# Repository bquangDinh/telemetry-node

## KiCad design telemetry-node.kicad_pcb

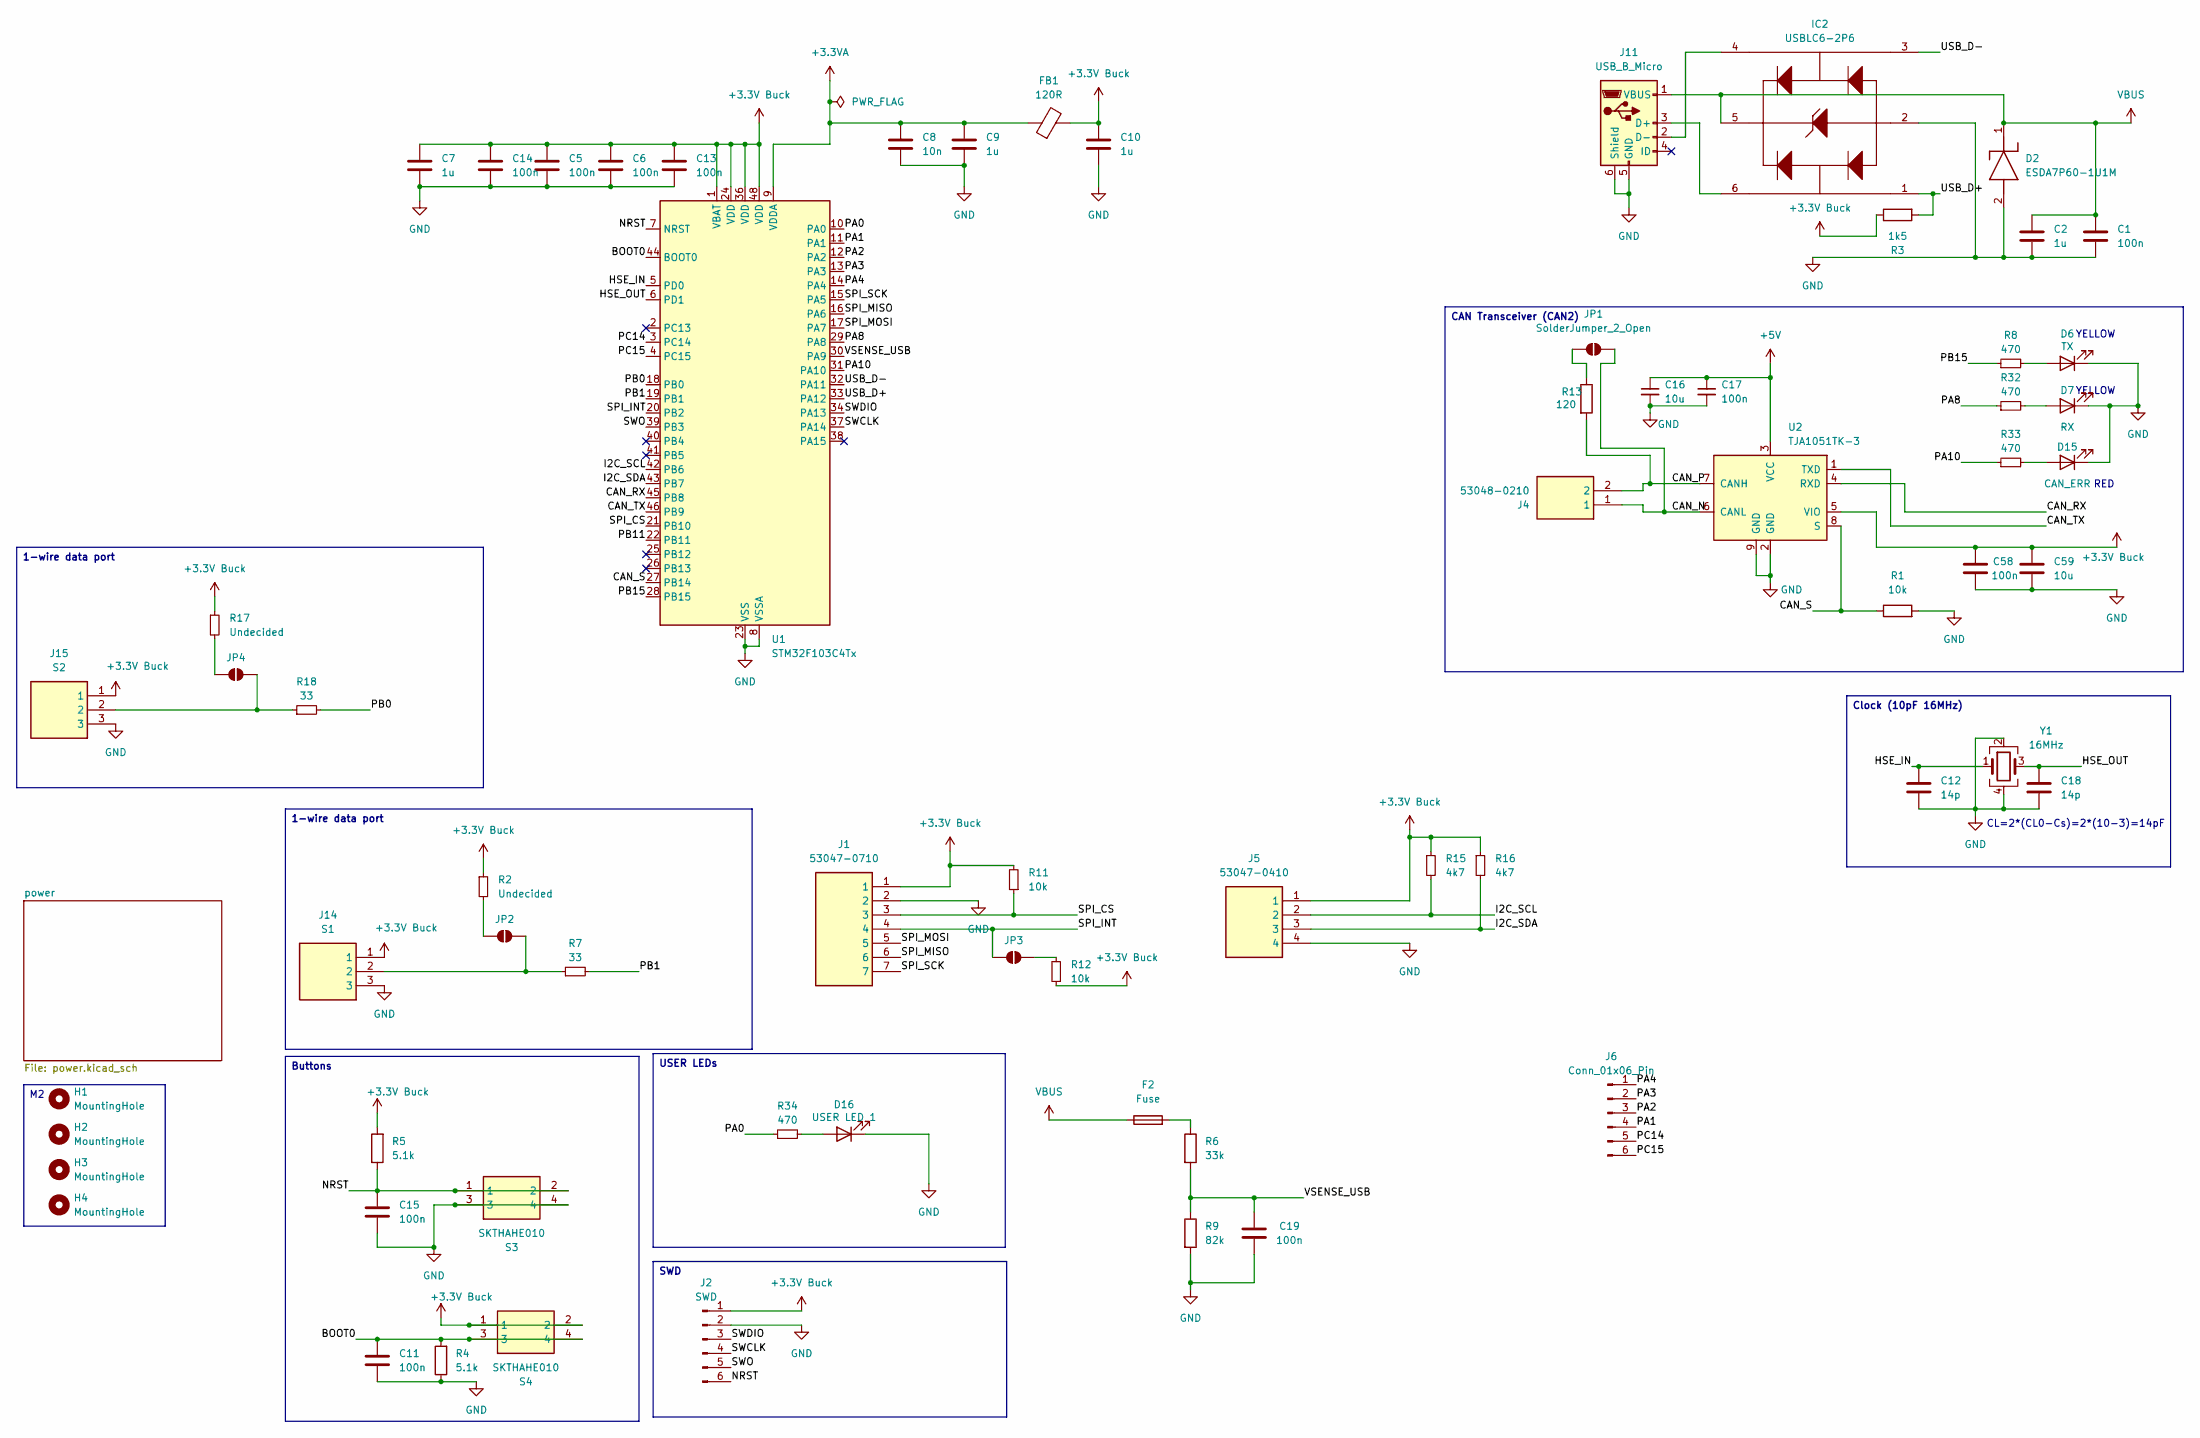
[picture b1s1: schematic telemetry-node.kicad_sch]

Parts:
C1, C5, C6, C11, C13, C14, C15, C17, C19, C58: 100n; C_0603_1608Metric_Pad1.08x0.95mm_HandSolder
C2, C7, C9, C10: 1u; C_0805_2012Metric_Pad1.18x1.45mm_HandSolder
C8: 10n; C_0603_1608Metric_Pad1.08x0.95mm_HandSolder
C12, C18: 14p; C_0603_1608Metric_Pad1.08x0.95mm_HandSolder
C16, C59: 10u; C_0805_2012Metric_Pad1.18x1.45mm_HandSolder
D2: ESDA7P60-1U1M; ESDA7P601U1M; Mouser Part Number 511-ESDA7P60-1U1M
D6: TX; LED_0805_2012Metric_Pad1.15x1.40mm_HandSolder
D7: RX; LED_0805_2012Metric_Pad1.15x1.40mm_HandSolder
D15: CAN_ERR; LED_0805_2012Metric_Pad1.15x1.40mm_HandSolder
D16: USER LED 1; LED_0805_2012Metric_Pad1.15x1.40mm_HandSolder
F2: Fuse; Fuse_0603_1608Metric_Pad1.05x0.95mm_HandSolder
FB1: 120R; L_0805_2012Metric_Pad1.05x1.20mm_HandSolder
H1, H2, H3, H4: MountingHole; MountingHole_2.2mm_M2
IC2: USBLC6-2P6; USBLC62P6; Mouser Part Number 511-USBLC6-2P6
J1: 53047-0710; 530470710; Mouser Part Number 538-53047-0710
J2: SWD; PinHeader_1x06_P2.00mm_Vertical
J4: 53048-0210; SHDRRA2W35P0X125_1X2_425X550X350P; Mouser Part Number 538-53048-0210
J5: 53047-0410; 530470410; Mouser Part Number 538-53047-0410
J6: Conn_01x06_Pin; PinHeader_1x06_P2.00mm_Vertical
J11: USB_B_Micro; USB_Micro-B_Wuerth_629105150521
J14: S1; 530470310; Mouser Part Number 538-53047-0310
J15: S2; 530470310; Mouser Part Number 538-53047-0310
JP1, JP2, JP3, JP4: SolderJumper_2_Open; SolderJumper-2_P1.3mm_Open_RoundedPad1.0x1.5mm
R1, R11, R12: 10k; R_0603_1608Metric_Pad0.98x0.95mm_HandSolder
R2, R17: Undecided; R_0603_1608Metric_Pad0.98x0.95mm_HandSolder
R3: 1k5; R_0603_1608Metric_Pad0.98x0.95mm_HandSolder
R4, R5: 5.1k; R_0603_1608Metric_Pad0.98x0.95mm_HandSolder
R6: 33k; R_0603_1608Metric_Pad0.98x0.95mm_HandSolder
R7, R18: 33; R_0603_1608Metric_Pad0.98x0.95mm_HandSolder
R8, R32, R33, R34: 470; R_0603_1608Metric_Pad0.98x0.95mm_HandSolder
R9: 82k; R_0603_1608Metric_Pad0.98x0.95mm_HandSolder
R13: 120; R_0603_1608Metric_Pad0.98x0.95mm_HandSolder
R15, R16: 4k7; R_0603_1608Metric_Pad0.98x0.95mm_HandSolder
S3, S4: SKTHAHE010; Mouser Part Number 688-SKTHAHE010
U1: STM32F103C4Tx; LQFP-48_7x7mm_P0.5mm
U2: TJA1051TK-3; DFN-8-1EP_3x3mm_P0.65mm_EP1.55x2.4mm
Y1: 16MHz; Crystal_SMD_3225-4Pin_3.2x2.5mm

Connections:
+3.3V Buck: C5.1, C6.1, C7.1, C10.1, C13.1, C14.1, C58.2, C59.2, FB1.2, J1.1, J2.1, J5.1, J14.1, J15.1, R2.1, R3.1, R5.2, R11.2, R12.1, R15.1, R16.1, R17.1, S4.1, S4.2, U1.1 (VBAT), U1.24 (VDD), U1.36 (VDD), U1.48 (VDD), U2.5 (VIO); also elsewhere on the board
+3.3VA: C8.1, C9.1, FB1.1, U1.9 (VDDA)
+5V: C16.1, C17.1, U2.3 (VCC); also elsewhere on the board
/BOOT0: C11.1, R4.2, S4.3, S4.4, U1.44 (BOOT0)
/CAN_N: J4.1, JP1.2 (B), U2.6 (CANL)
/CAN_P: J4.2, R13.2, U2.7 (CANH)
/CAN_RX: U1.45 (PB8), U2.4 (RXD)
/CAN_S: R1.1, U1.27 (PB14), U2.8 (S)
/CAN_TX: U1.46 (PB9), U2.1 (TXD)
/HSE_IN: C12.1, U1.5 (PD0), Y1.1
/HSE_OUT: C18.1, U1.6 (PD1), Y1.3
/I2C_SCL: J5.2, R15.2, U1.42 (PB6)
/I2C_SDA: J5.3, R16.2, U1.43 (PB7)
/NRST: C15.1, J2.6, R5.1, S3.1, S3.2, U1.7 (NRST)
/PA0: R34.1, U1.10 (PA0)
/PA1: J6.4, U1.11 (PA1)
/PA2: J6.3, U1.12 (PA2)
/PA3: J6.2, U1.13 (PA3)
/PA4: J6.1, U1.14 (PA4)
/PA8: R32.1, U1.29 (PA8)
/PA10: R33.1, U1.31 (PA10)
/PB0: R18.2, U1.18 (PB0)
/PB1: R7.2, U1.19 (PB1)
/PB11: U1.22 (PB11)
/PB15: R8.1, U1.28 (PB15)
/PC14: J6.5, U1.3 (PC14)
/PC15: J6.6, U1.4 (PC15)
/SPI_CS: J1.3, R11.1, U1.21 (PB10)
/SPI_INT: J1.4, JP3.1 (A), U1.20 (PB2)
/SPI_MISO: J1.6, U1.16 (PA6)
/SPI_MOSI: J1.5, U1.17 (PA7)
/SPI_SCK: J1.7, U1.15 (PA5)
/SWCLK: J2.4, U1.37 (PA14)
/SWDIO: J2.3, U1.34 (PA13)
/SWO: J2.5, U1.39 (PB3)
/USB_D+: IC2.1 (I/O1_1), R3.2, U1.33 (PA12)
/USB_D-: IC2.3 (I/O2_1), U1.32 (PA11)
/VSENSE_USB: C19.1, R6.2, R9.1, U1.30 (PA9)
GND: C1.2, C2.2, C5.2, C6.2, C7.2, C8.2, C9.2, C10.2, C11.2, C12.2, C13.2, C14.2, C15.2, C16.2, C17.2, C18.2, C19.2, C58.1, C59.1, D2.2 (A), D6.1 (K), D7.1 (K), D15.1 (K), D16.1 (K), IC2.2 (GND), J1.2, J2.2, J5.4, J11.5 (GND), J11.6 (Shield), J14.3, J15.3, R1.2, R4.1, R9.2, S3.3, S3.4, U1.8 (VSSA), U1.23 (VSS), U1.35 (VSS), U1.47 (VSS), U2.2 (GND), U2.9 (GND), Y1.2, Y1.4; also elsewhere on the board
unnamed: D6.2 (A), R8.2
unnamed: D7.2 (A), R32.2
unnamed: D15.2 (A), R33.2
unnamed: D16.2 (A), R34.2
unnamed: F2.2, R6.1
unnamed: IC2.6 (I/O1_2), J11.3 (D+)
unnamed: IC2.4 (I/O2_2), J11.2 (D-)
unnamed: JP1.1 (A), R13.1
unnamed: JP2.1 (A), R2.2
unnamed: J14.2, JP2.2 (B), R7.1
unnamed: JP3.2 (B), R12.2
unnamed: JP4.1 (A), R17.2
unnamed: J15.2, JP4.2 (B), R18.1
VBUS: C1.1, C2.1, D2.1 (K), F2.1, IC2.5 (VBUS), J11.1 (VBUS)

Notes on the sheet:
RED
YELLOW
CL=2*(CL0-Cs)=2*(10-3)=14pF
CAN Transceiver (CAN2)
Buttons
USER LEDs
1-wire data port
Clock (10pF 16MHz)
SWD

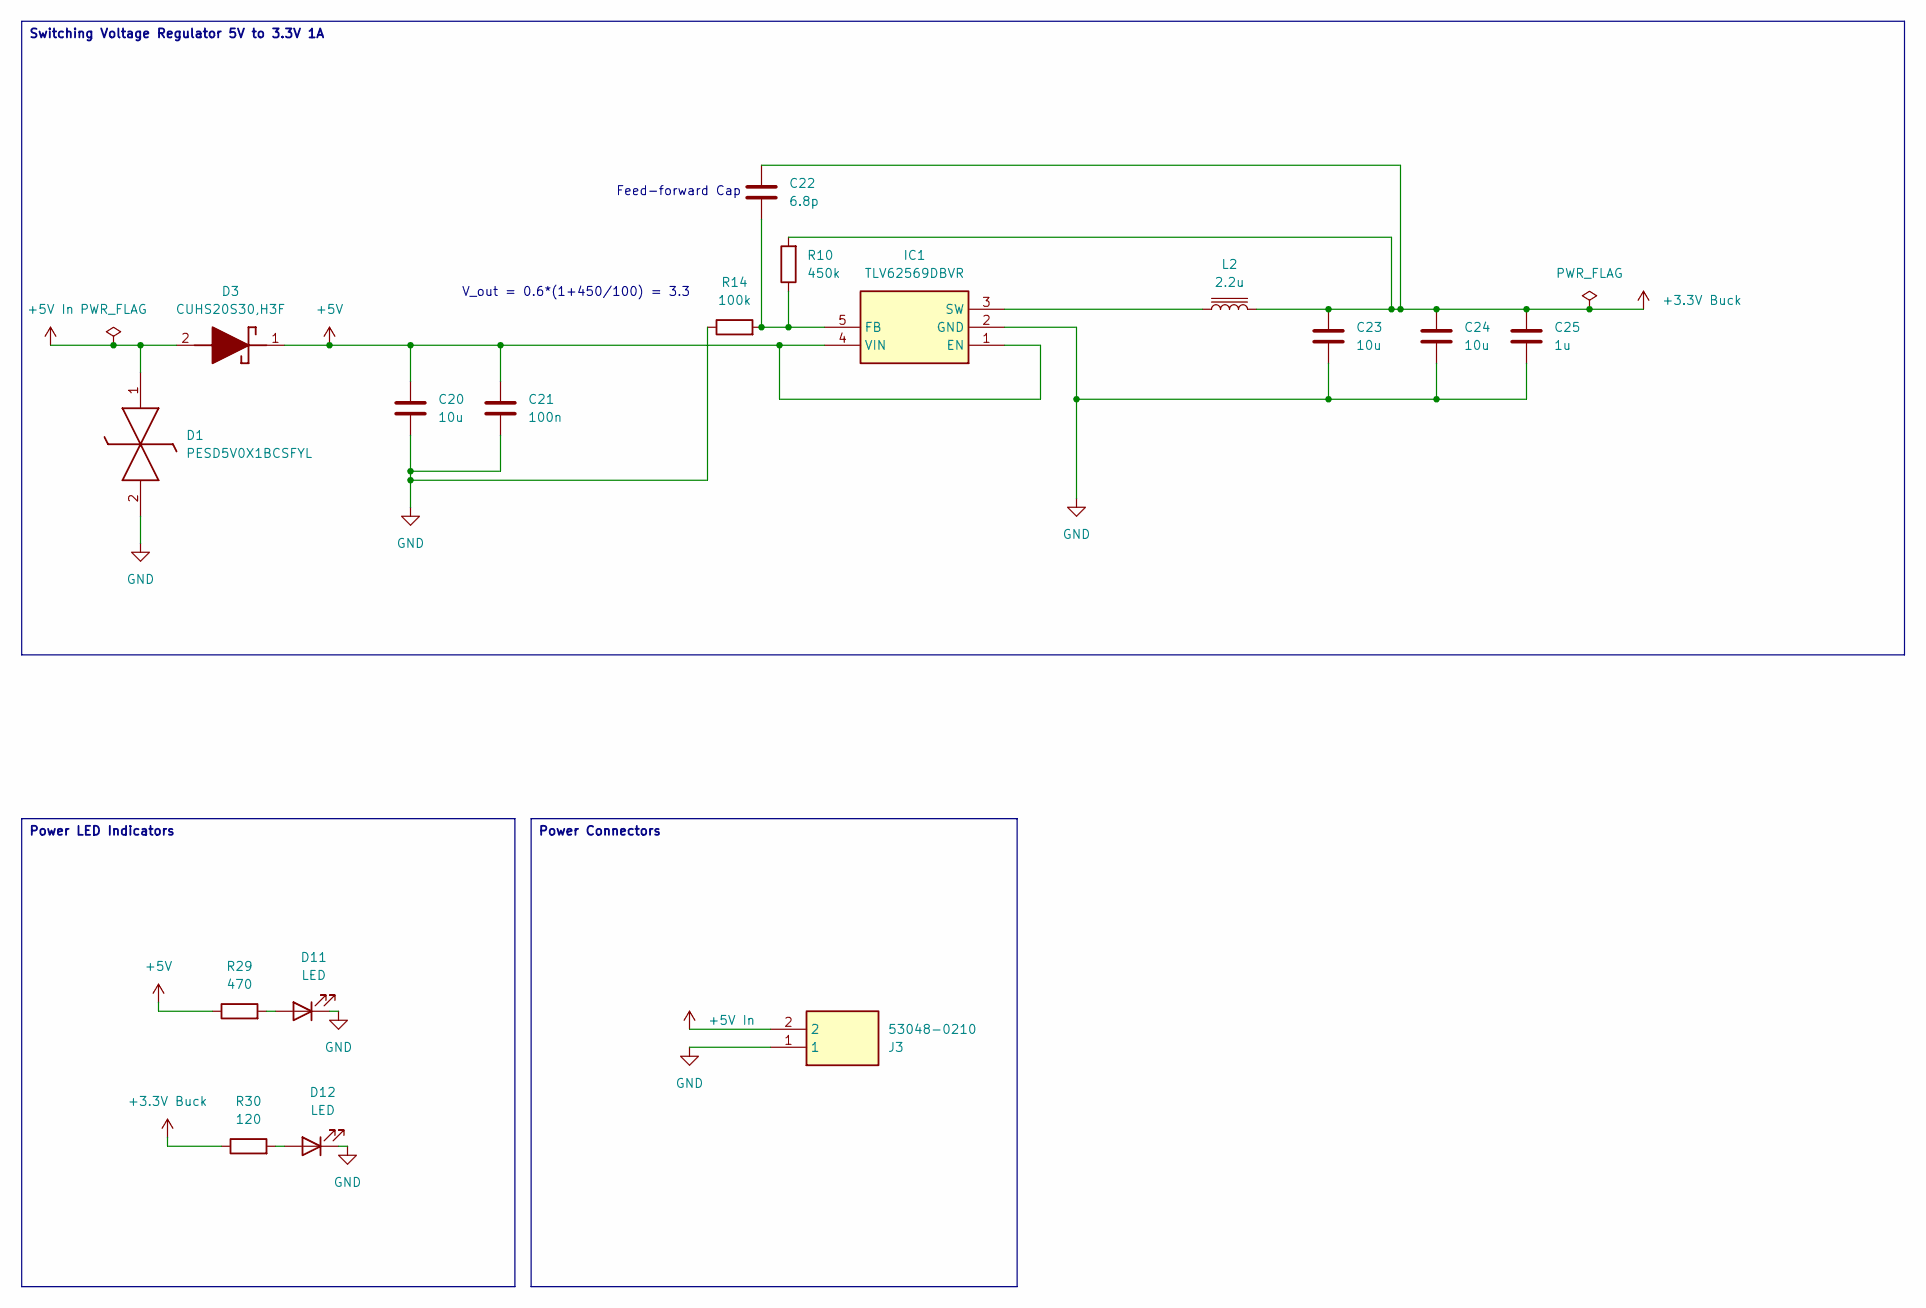
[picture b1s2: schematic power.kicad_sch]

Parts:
C20, C23, C24: 10u; C_0805_2012Metric_Pad1.18x1.45mm_HandSolder
C21: 100n; C_0603_1608Metric_Pad1.08x0.95mm_HandSolder
C22: 6.8p; C_0805_2012Metric_Pad1.18x1.45mm_HandSolder
C25: 1u; C_0805_2012Metric_Pad1.18x1.45mm_HandSolder
D1: PESD5V0X1BCSFYL; PMEG3005AESFYL; Mouser Part Number 771-PESD5V0X1BCSFYL
D3: CUHS20S30,H3F; CUHS20S40H3F; Mouser Part Number 757-CUHS20S30H3F
D11, D12: LED; LED_0805_2012Metric_Pad1.15x1.40mm_HandSolder
IC1: TLV62569DBVR; SOT95P280X145-5N; Mouser Part Number 595-TLV62569DBVR
J3: 53048-0210; SHDRRA2W35P0X125_1X2_425X550X350P; Mouser Part Number 538-53048-0210
L2: 2.2u; LQM2HPZ3R3MJ0B
R10: 450k; R_0805_2012Metric_Pad1.20x1.40mm_HandSolder
R14: 100k; R_0805_2012Metric_Pad1.20x1.40mm_HandSolder
R29: 470; R_0603_1608Metric_Pad0.98x0.95mm_HandSolder
R30: 120; R_0603_1608Metric_Pad0.98x0.95mm_HandSolder

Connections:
+3.3V Buck: C22.2, C23.1, C24.1, C25.1, L2.2, R10.2, R30.1; also elsewhere on the board
+5V: C20.2, C21.1, D3.1 (K), IC1.1 (EN), IC1.4 (VIN), R29.1; also elsewhere on the board
+5V In: D1.1 (K1), D3.2 (A), J3.2
GND: C20.1, C21.2, C23.2, C24.2, C25.2, D1.2 (K2), D11.1 (K), D12.1 (K), IC1.2 (GND), J3.1, R14.1; also elsewhere on the board
unnamed: D11.2 (A), R29.2
unnamed: D12.2 (A), R30.2
unnamed: C22.1, IC1.5 (FB), R10.1, R14.2
unnamed: IC1.3 (SW), L2.1

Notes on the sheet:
Feed-forward Cap
V_out = 0.6*(1+450/100) = 3.3
Power LED Indicators
Power Connectors
Switching Voltage Regulator 5V to 3.3V 1A

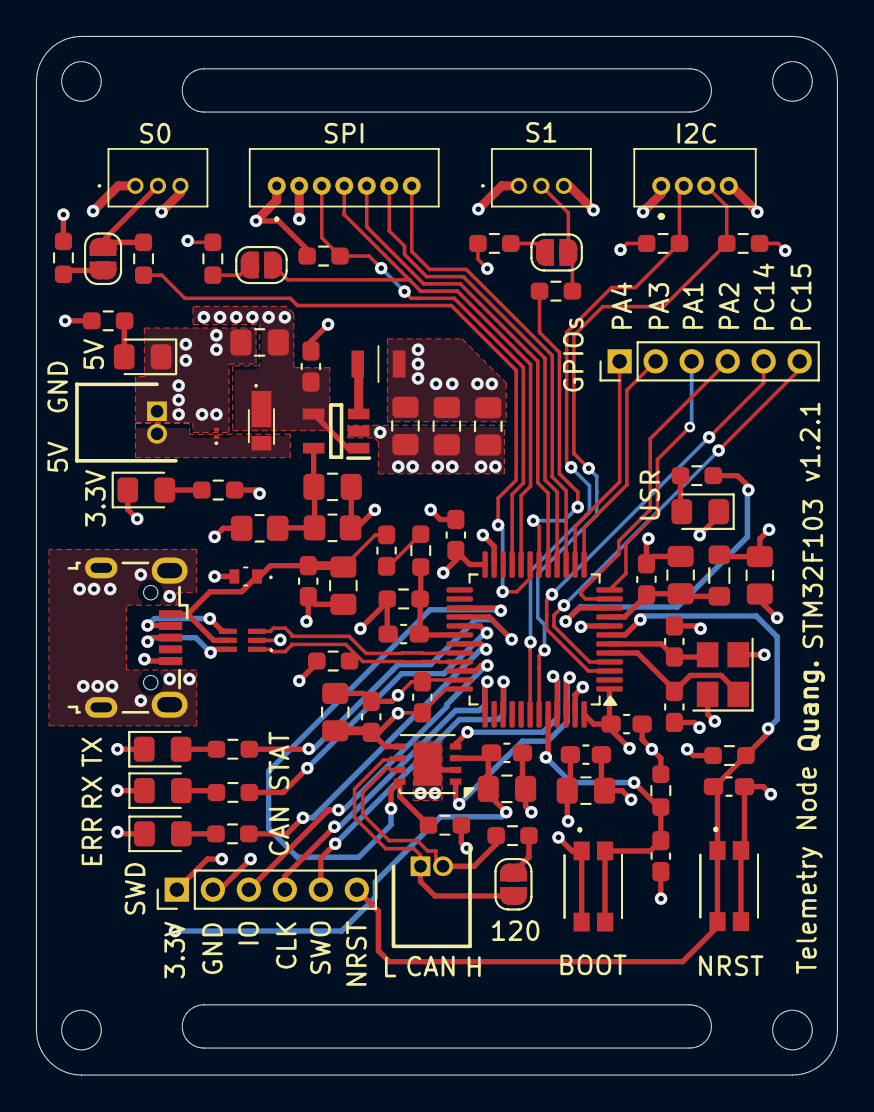
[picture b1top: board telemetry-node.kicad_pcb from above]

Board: 4 copper layers, 44.5 x 57.7 mm, 84 parts (0 on the bottom side), 57 nets.

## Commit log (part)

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2026-02-15 Changed things
2026-02-17 Fixed things
2026-03-14 Added temp
2026-03-26 Changed .gitignores
